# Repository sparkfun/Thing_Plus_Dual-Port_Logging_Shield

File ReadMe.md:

SparkFun Thing Plus Dual-Port Logging Shield
========================================

[*SparkFun Thing Plus Dual-Port Logging Shield (DEV-19217)*](https://www.sparkfun.com/products/19217)

The SparkFun Thing Plus Dual-Port Logging Shield is a Thing Plus/Feather compatible board that allows you to access your microSD card over **_both_** SPI and USB-C! It is designed to be mounted on or under one of our [Thing Plus boards](https://www.sparkfun.com/thing_plus). You can log data to and read data from your microSD card over SPI as usual, using your favorite Arduino SD library. But you can also connect it to your computer via USB-C and read and write files at **_up to 35 MBytes/second_**! The write speed is card-dependent but, in our tests, we've routinely seen write speeds around 20MB/s.

Repository Contents
-------------------

* **/Documents** - Data sheets, additional product information
* **/Firmware/Dual-Port_microSD_Shield** - Firmware for the ATtiny 
* **/Hardware** - Eagle design files (.brd, .sch)
* **/img** - Final production files.

Documentation
--------------
* **[Library](https://github.com/sparkfun/SparkFun_Dual-Port_Logging_Shield_Arduino_Library)** - Arduino library for the SparkFun Thing Plus Dual-Port Logging Shield.
* **[Hookup Guide](https://learn.sparkfun.com/tutorials/thing-plus-dual-port-logging-shield-hookup-guide)** - Basic hookup guide for the SparkFun Thing Plus Dual-Port Logging Shield.

License Information
-------------------

This product is _**open source**_! 

Please review the LICENSE.md file for license information. 

If you have any questions or concerns on licensing, please contact technical support on our [SparkFun forums](https://forum.sparkfun.com/viewforum.php?f=152).

Distributed as-is; no warranty is given.

- Your friends at SparkFun.

_<COLLABORATION CREDIT>_

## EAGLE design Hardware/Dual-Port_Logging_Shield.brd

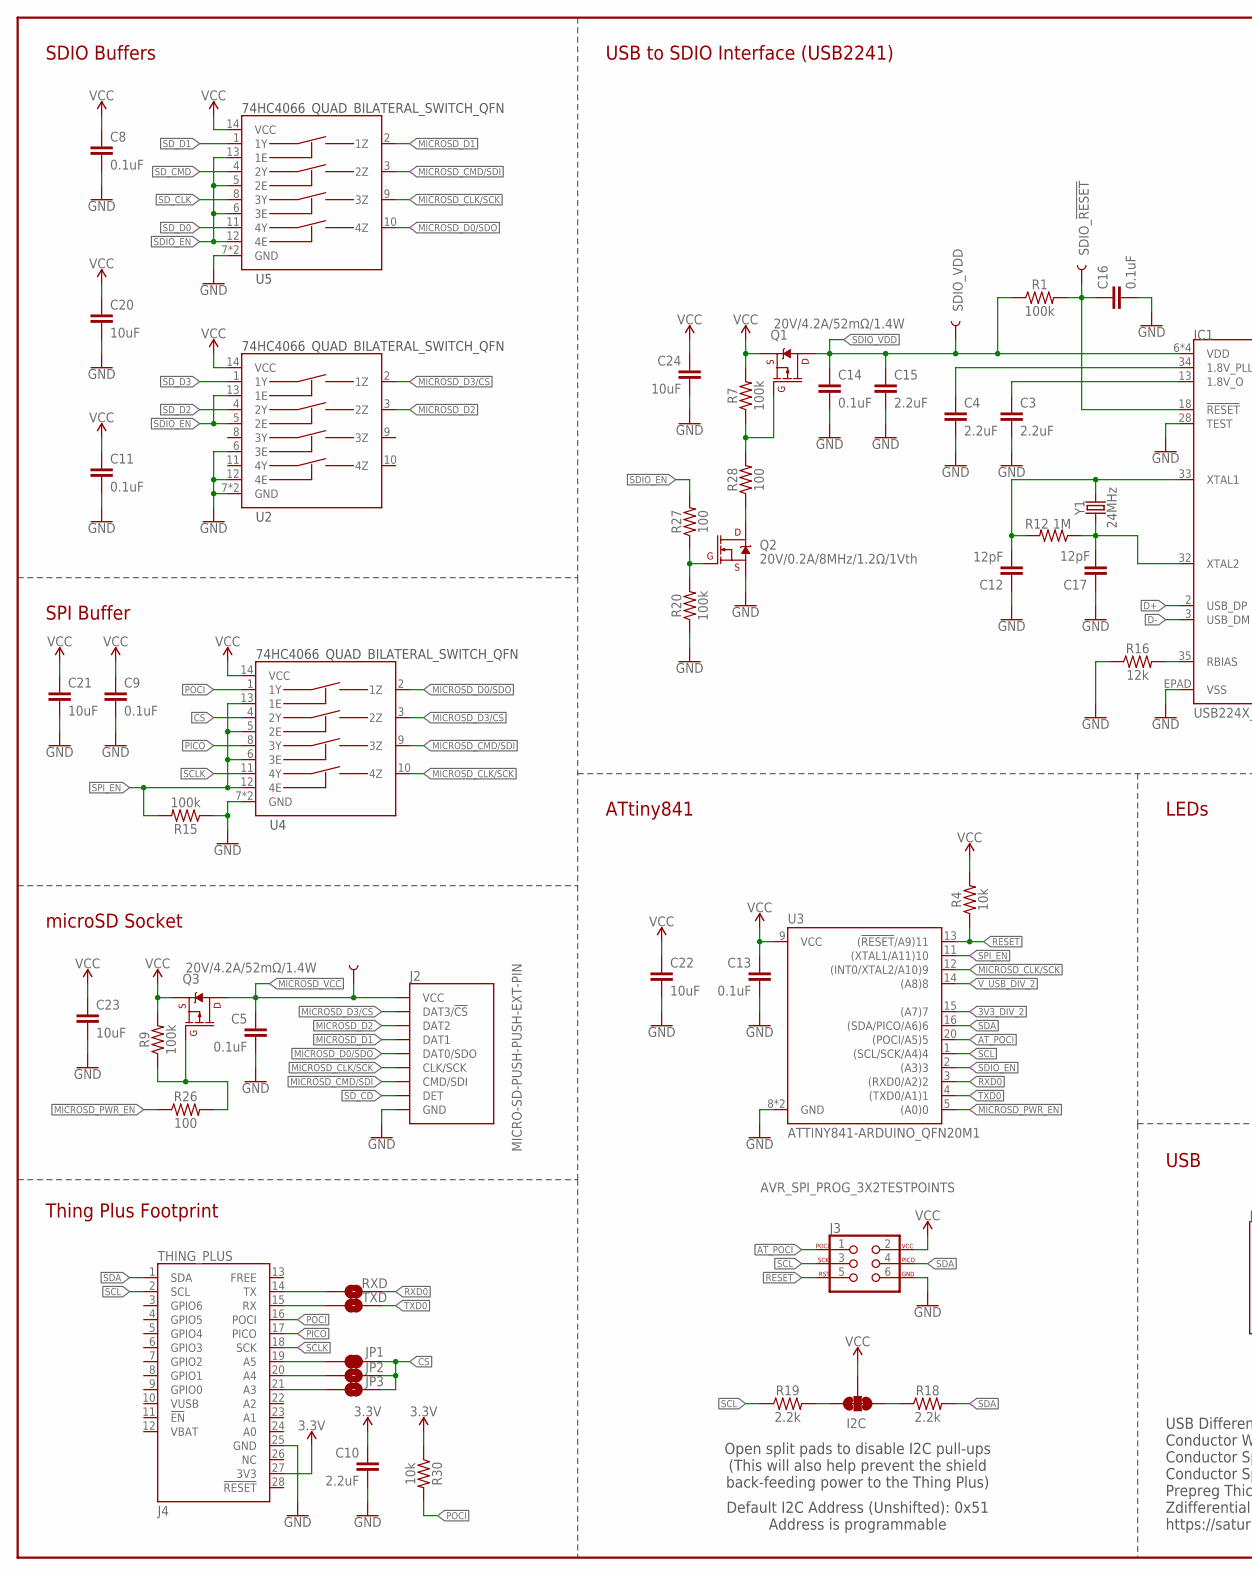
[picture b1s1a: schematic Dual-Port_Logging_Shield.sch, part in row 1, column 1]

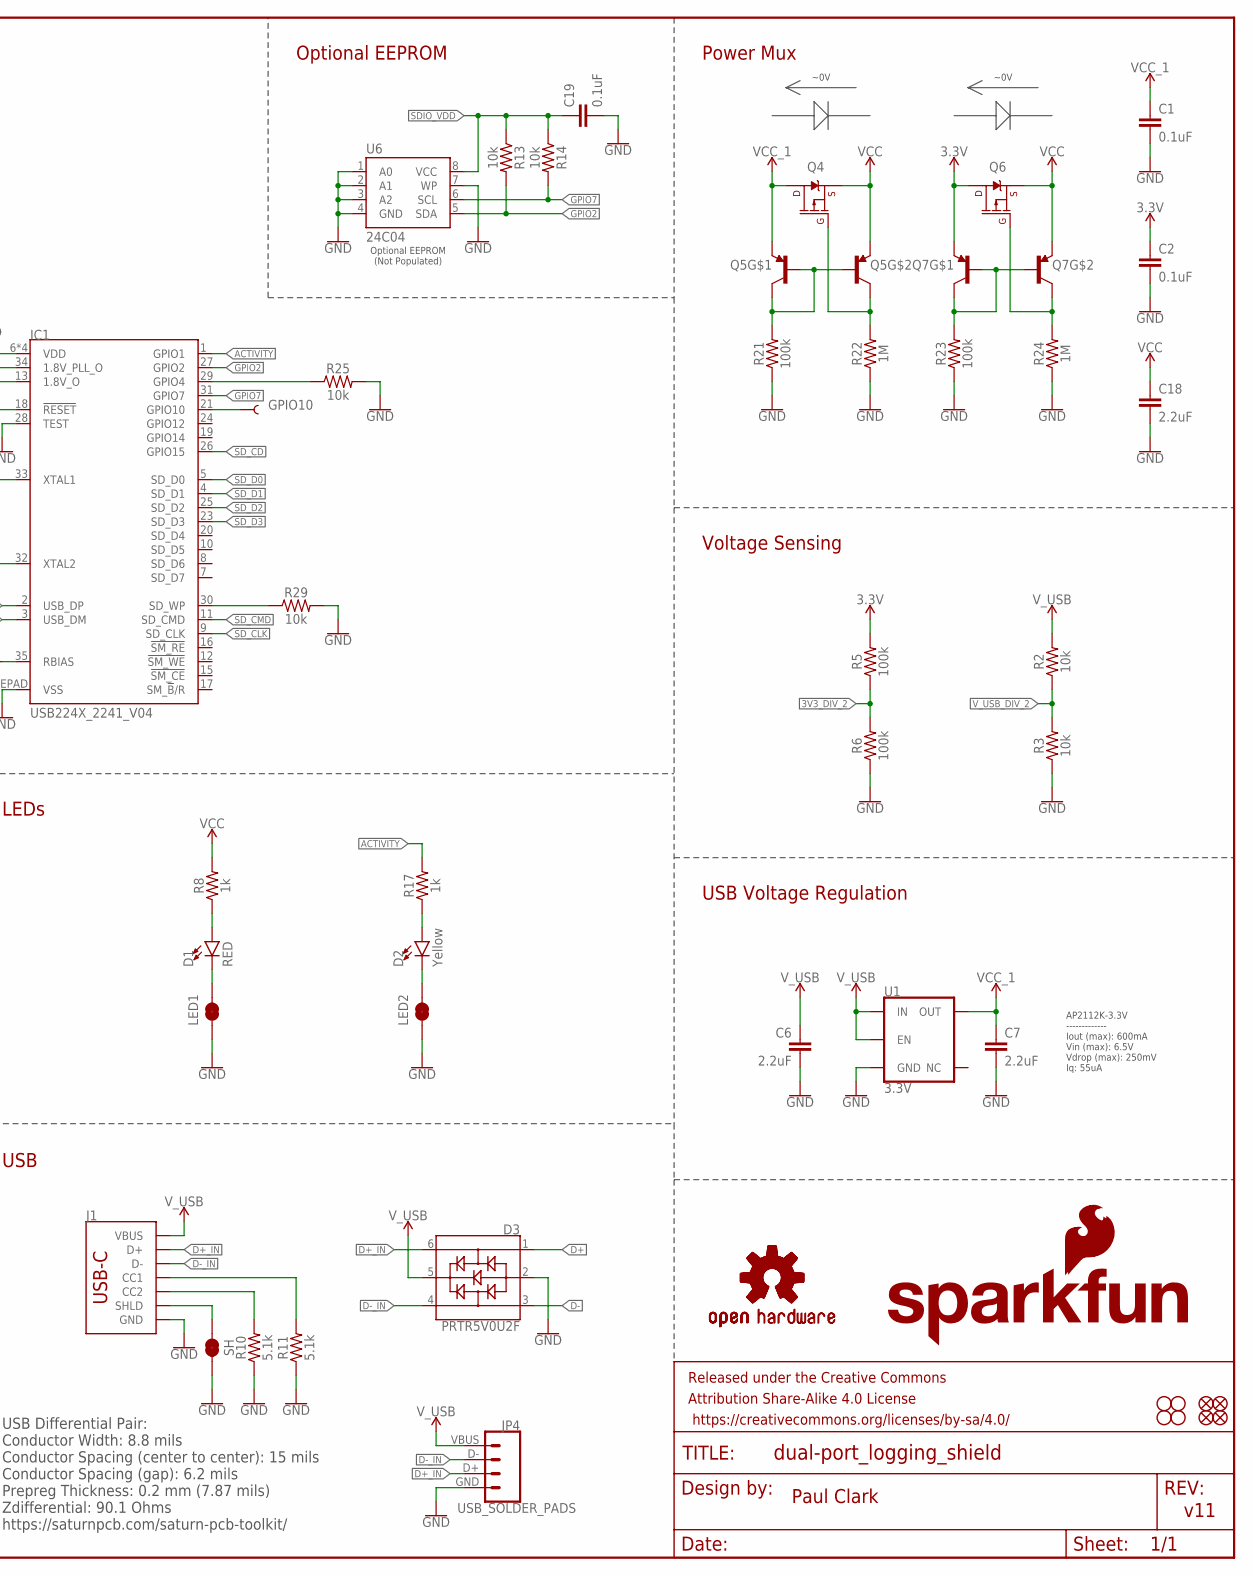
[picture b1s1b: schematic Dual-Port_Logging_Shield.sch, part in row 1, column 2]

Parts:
C1, C2, C5, C8, C9, C11, C13, C14, C16, C19: 0.1uF; 0402-TIGHT
C3, C4, C6, C7, C10, C15, C18: 2.2uF; 0402-TIGHT
C12, C17: 12pF; 0402-TIGHT
C20, C21, C22, C23, C24: 10uF; 0402-TIGHT
D1: RED; LED-0603
D2: Yellow; LED-0603
D3: PRTR5V0U2F; SOT886
FD1, FD2, FD3, FD4: FIDUCIALUFIDUCIAL; FIDUCIAL-MICRO
FRAME1: FRAME-LEDGER; CREATIVE_COMMONS
GPIO10: TEST-POINT3; PAD.03X.03
H1, H2, H3, H4: STAND-OFF
I2C: JUMPER-SMT_3_2-NC_TRACE_SILK; SMT-JUMPER_3_2-NC_TRACE_SILK
IC1: USB224X_2241_V04; 36-QFN
J1: USB_C_4-LAYER_PADS; USB-C-16P_4LAYER-PADS
J2: MICRO-SD-PUSH-PUSH-EXT-PIN; MICROSD-EXTERNALPIN
J3: AVR_SPI_PROG_3X2TESTPOINTS; 2X3_TEST_POINTS
J4: THING_PLUS
JP1: JUMPER-SMT_2_NC_TRACE_SILK; SMT-JUMPER_2_NC_TRACE_SILK
JP2, JP3: JUMPER-SMT_2_NO_SILK; SMT-JUMPER_2_NO_SILK
JP4: USB_SOLDER_PADS; USB-SOLDER-PADS
LED1, LED2: JUMPER-SMT_2_NC_TRACE_SILK; SMT-JUMPER_2_NC_TRACE_SILK
LOGO2, LOGO3: OSHW-LOGOMINI; OSHW-LOGO-MINI
LOGO4: SFE_LOGO_FLAME.2_INCH; SFE_LOGO_FLAME_.2
LOGO5: SFE_LOGO_NAME_FLAME.1_INCH; SFE_LOGO_NAME_FLAME_.1
MICROSD_VCC: TEST-POINT3; PAD.03X.03
Q1, Q3, Q4, Q6: 20V/4.2A/52mΩ/1.4W; SOT23-3
Q2: 20V/0.2A/8MHz/1.2Ω/1Vth; SOT-416FL
Q5, Q7: TRANS_PNP_DUALSOT-363; SOT363_PHILIPS
R1, R5, R6, R7, R9, R15, R20, R21, R23: 100k; 0402-TIGHT
R2, R3, R4, R13, R14, R25, R29, R30: 10k; 0402-TIGHT
R8, R17: 1k; 0402-TIGHT
R10, R11: 5.1k; 0402-TIGHT
R12, R22, R24: 1M; 0402-TIGHT
R16: 12k; 0603
R18, R19: 2.2k; 0402-TIGHT
R26, R27, R28: 100; 0402-TIGHT
RXD: JUMPER-SMT_2_NO_SILK; SMT-JUMPER_2_NO_SILK
SDIO_!RESET!: TEST-POINT3; PAD.03X.03
SDIO_VDD: TEST-POINT3; PAD.03X.03
SH: JUMPER-SMT_2_NC_TRACE_NO-SILK; SMT-JUMPER_2_NC_TRACE_NO-SILK
TXD: JUMPER-SMT_2_NO_SILK; SMT-JUMPER_2_NO_SILK
U1: 3.3V; SOT23-5
U2, U4, U5: 74HC4066_QUAD_BILATERAL_SWITCH_QFN; 14-QFN
U3: ATTINY841-ARDUINO_QFN20M1; QFN20_20M1
U6: 24C04; SO08
Y1: 24MHz; CRYSTAL-SMD-2.0X1.6MM

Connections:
3.3V: C2.1, C10.1, J4.27 (3V3), Q6.3 (D), Q7.1 (E), R5.2, R30.1
3V3_DIV_2: R5.1, R6.2, U3.15 ((A7)7)
!CS!: JP1.2, JP2.2, JP3.2, U4.4 (2Y)
!RESET!: J3.5, R4.1, U3.13 ((!RESET!/A9)11)
ACTIVITY: IC1.1 (GPIO1), R17.2
AT_POCI: J3.1, U3.20 ((POCI/A5)5)
D+: D3.1, IC1.2 (USB_DP)
D+_IN: D3.6, J1.A6 (D+), J1.B6 (D+), JP4.D+ (3)
D-: D3.3, IC1.3 (USB_DM)
D-_IN: D3.4, J1.A7 (D-), J1.B7 (D-), JP4.D- (2)
GND: C1.2, C2.2, C3.2, C4.2, C5.2, C6.2, C7.2, C8.2, C9.2, C10.2, C11.2, C12.1, C13.2, C14.2, C15.2, C16.2, C17.1, C18.2, C19.2, C20.2, C21.2, C22.2, C23.2, C24.2, D3.2, IC1.28 (TEST), IC1.EPAD (VSS), J1.GND, J1.GND2 (GND), J2.6 (GND), J2.10 (GND), J2.11 (GND), J2.12 (GND), J2.13 (GND), J3.6, J4.25 (GND), JP4.GND (4), LED1.1, LED2.1, Q2.2 (S), R3.1, R6.1, R10.1, R11.1, R15.1, R16.1, R20.1, R21.1, R22.1, R23.1, R24.1, R25.2, R29.2, SH.2, U1.2 (GND), U2.6 (3E), U2.7 (GND), U2.12 (4E), U2.EPAD (GND), U3.8 (GND), U3.PAD (GND), U4.7 (GND), U4.EPAD (GND), U5.7 (GND), U5.EPAD (GND), U6.1 (A0), U6.2 (A1), U6.3 (A2), U6.4 (GND), U6.7 (WP)
GPIO2: IC1.27 (GPIO2), R13.2, U6.5 (SDA)
GPIO4: IC1.29 (GPIO4), R25.1
GPIO7: IC1.31 (GPIO7), R14.2, U6.6 (SCL)
GPIO10: GPIO10.1, IC1.21 (GPIO10)
MICROSD_CLK/SCK: J2.5 (CLK/SCK), U3.12 ((INT0/XTAL2/A10)9), U4.10 (4Z), U5.9 (3Z)
MICROSD_CMD/SDI: J2.3 (CMD/SDI), U4.9 (3Z), U5.3 (2Z)
MICROSD_D0/SDO: J2.7 (DAT0/SDO), U4.2 (1Z), U5.10 (4Z)
MICROSD_D1: J2.8 (DAT1), U5.2 (1Z)
MICROSD_D2: J2.1 (DAT2), U2.3 (2Z)
MICROSD_D3/!CS!: J2.2 (DAT3/!CS!), U2.2 (1Z), U4.3 (2Z)
MICROSD_PWR_EN: R26.1, U3.5 ((A0)0)
MICROSD_VCC: C5.1, J2.4 (VCC), MICROSD_VCC.1, Q3.3 (D)
unnamed: J1.A5 (CC1), R11.2
unnamed: J1.B5 (CC2), R10.2
unnamed: C3.1, IC1.13 (1.8V_O)
unnamed: C4.1, IC1.34 (1.8V_PLL_O)
unnamed: Q5.2 (B), Q5.5 (B), Q5.6 (C), R21.2
unnamed: Q3.1 (G), R9.1, R26.2
unnamed: Q2.1 (G), R20.2, R27.1
unnamed: Q2.3 (D), R28.1
unnamed: J4.19 (A5), JP1.1
unnamed: J4.20 (A4), JP2.1
unnamed: J4.21 (A3), JP3.1
unnamed: J1.SHLD1 (SHLD), J1.SHLD2 (SHLD), J1.SHLD3 (SHLD), J1.SHLD4 (SHLD), SH.1
unnamed: Q4.1 (G), Q5.3 (C), R22.2
unnamed: I2C.3, R19.2
unnamed: Q7.2 (B), Q7.5 (B), Q7.6 (C), R23.2
unnamed: I2C.1, R18.1
unnamed: Q1.1 (G), R7.1, R28.2
unnamed: D2.A, R17.1
unnamed: D2.C, LED2.2
unnamed: IC1.30 (SD_WP), R29.1
unnamed: D1.A, R8.1
unnamed: IC1.35 (RBIAS), R16.2
unnamed: J4.14 (TX), RXD.1
unnamed: J4.15 (RX), TXD.1
unnamed: D1.C, LED1.2
unnamed: Q6.1 (G), Q7.3 (C), R24.2
PICO: J4.17 (PICO), U4.8 (3Y)
POCI: J4.16 (POCI), R30.2, U4.1 (1Y)
RXD0: RXD.2, U3.3 ((RXD0/A2)2)
SCL: J3.3, J4.2 (SCL), R19.1, U3.1 ((SCL/SCK/A4)4)
SCLK: J4.18 (SCK), U4.11 (4Y)
SDA: J3.4, J4.1 (SDA), R18.2, U3.16 ((SDA/PICO/A6)6)
SDIO_!RESET!: C16.1, IC1.18 (!RESET!), R1.2, SDIO_!RESET!.1
SDIO_EN: R27.2, U2.5 (2E), U2.13 (1E), U3.2 ((A3)3), U5.5 (2E), U5.6 (3E), U5.12 (4E), U5.13 (1E)
SDIO_VDD: C14.1, C15.1, C19.1, IC1.6 (VDD), IC1.14 (VDD), IC1.22 (VDD), IC1.36 (VDD), Q1.3 (D), R1.1, R13.1, R14.1, SDIO_VDD.1, U6.8 (VCC)
SD_!CD!: IC1.26 (GPIO15), J2.9 (DET)
SD_CLK: IC1.9 (SD_CLK), U5.8 (3Y)
SD_CMD: IC1.11 (SD_CMD), U5.4 (2Y)
SD_D0: IC1.5 (SD_D0), U5.11 (4Y)
SD_D1: IC1.4 (SD_D1), U5.1 (1Y)
SD_D2: IC1.25 (SD_D2), U2.4 (2Y)
SD_D3: IC1.23 (SD_D3), U2.1 (1Y)
SPI_EN: R15.2, U3.11 ((XTAL1/A11)10), U4.5 (2E), U4.6 (3E), U4.12 (4E), U4.13 (1E)
TXD0: TXD.2, U3.4 ((TXD0/A1)1)
VCC: C8.1, C9.1, C11.1, C13.1, C18.1, C20.1, C21.1, C22.1, C23.1, C24.1, I2C.2, J3.2, Q1.2 (S), Q3.2 (S), Q4.2 (S), Q5.4 (E), Q6.2 (S), Q7.4 (E), R4.2, R7.2, R8.2, R9.2, U2.14 (VCC), U3.9 (VCC), U4.14 (VCC), U5.14 (VCC)
VCC_1: C1.1, C7.1, Q4.3 (D), Q5.1 (E), U1.5 (OUT)
V_USB: C6.1, D3.5, J1.VBUS1 (VBUS), J1.VBUS2 (VBUS), JP4.VBUS (1), R2.2, U1.1 (IN), U1.3 (EN)
V_USB_DIV_2: R2.1, R3.2, U3.14 ((A8)8)
XTAL1: C12.2, IC1.33 (XTAL1), R12.2, Y1.3 (2)
XTAL2: C17.2, IC1.32 (XTAL2), R12.1, Y1.1

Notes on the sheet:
Paul Clark
v11
Thing Plus Footprint
Voltage Sensing
USB to SDIO Interface (USB2241)
microSD Socket
SDIO Buffers
Power Mux
USB
USB Voltage Regulation
SPI Buffer
ATtiny841
AP2112K-3.3V ------------- Iout (max): 600mA Vin (max): 6.5V Vdrop (max): 250mV Iq: 55uA
LEDs
Open split pads to disable I2C pull-ups (This will also help prevent the shield back-feeding power to the Thing Plus)
~0V
Optional EEPROM (Not Populated)
Optional EEPROM
Default I2C Address (Unshifted): 0x51 Address is programmable
USB Differential Pair: Conductor Width: 8.8 mils Conductor Spacing (center to center): 15 mils Conductor Spacing (gap): 6.2 mils Prepreg Thickness: 0.2 mm (7.87 mils) Zdifferential: 90.1 Ohms https://saturnpcb.com/saturn-pcb-toolkit/

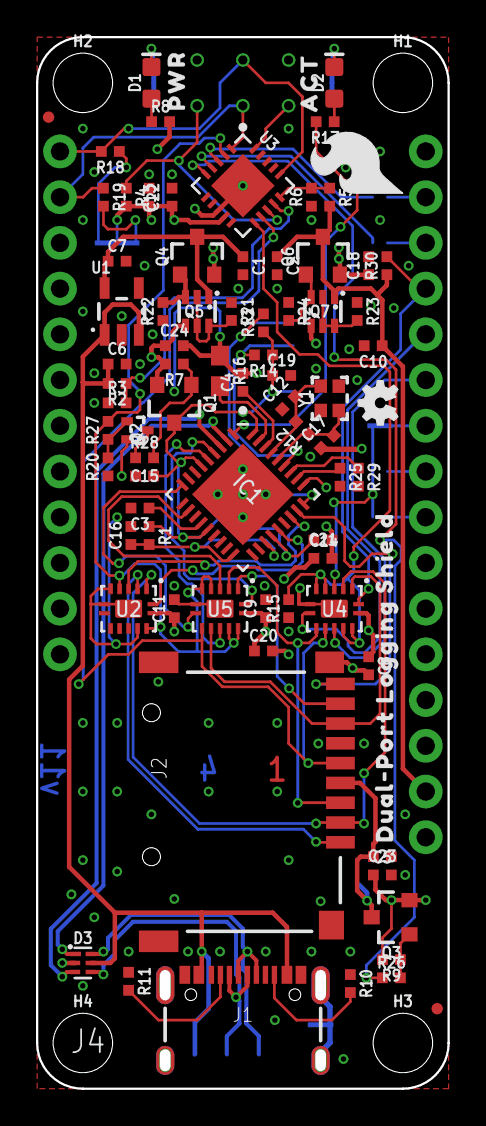
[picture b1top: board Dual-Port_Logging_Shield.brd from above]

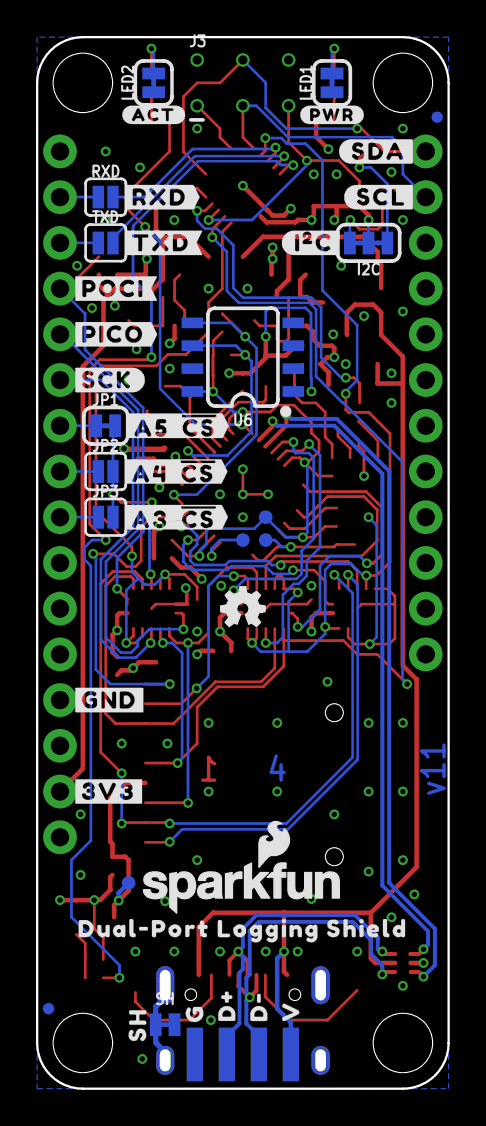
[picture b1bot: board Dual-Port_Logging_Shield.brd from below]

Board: 4 copper layers, 22.9 x 58.4 mm, 128 parts (41 on the bottom side), 73 nets.

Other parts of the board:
LOGO1: SPECIAL_INSTRUCTIONS-ORDERING; ORDERING_INSTRUCTIONS
U$1: #SDA#0
U$2: #SCL#1
U$3: #POCI#0
U$4: #PICO#1
U$5: #SCK#2
U$6, U$14: DUAL#PORT_LOGGING_SHIELD0
U$7: #GND#0
U$8: #3V3#1
U$9: #RXD#0
U$10: #TXD#1
U$11: PWR0
U$12: ACT0
U$13: #I�C#0
U$15: #PWR#0
U$16: #ACT#0
U$17: #A5__#CS##0
U$18: #A4__#CS##6
U$19: #A3__#CS##6
U$20: SH0
U$21: G0
U$22: V0
U$23: D#0
U$25: D#1

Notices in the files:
parts and their libraries:
SparkFun-Aesthetics: Licensing: Creative Commons ShareAlike 4.0 International - https://creativecommons.org/licenses/by-sa/4.0
SparkFun-Aesthetics: Released under the Creative Commons Attribution Share-Alike 4.0 License
SparkFun-Aesthetics: https://creativecommons.org/licenses/by-sa/4.0
